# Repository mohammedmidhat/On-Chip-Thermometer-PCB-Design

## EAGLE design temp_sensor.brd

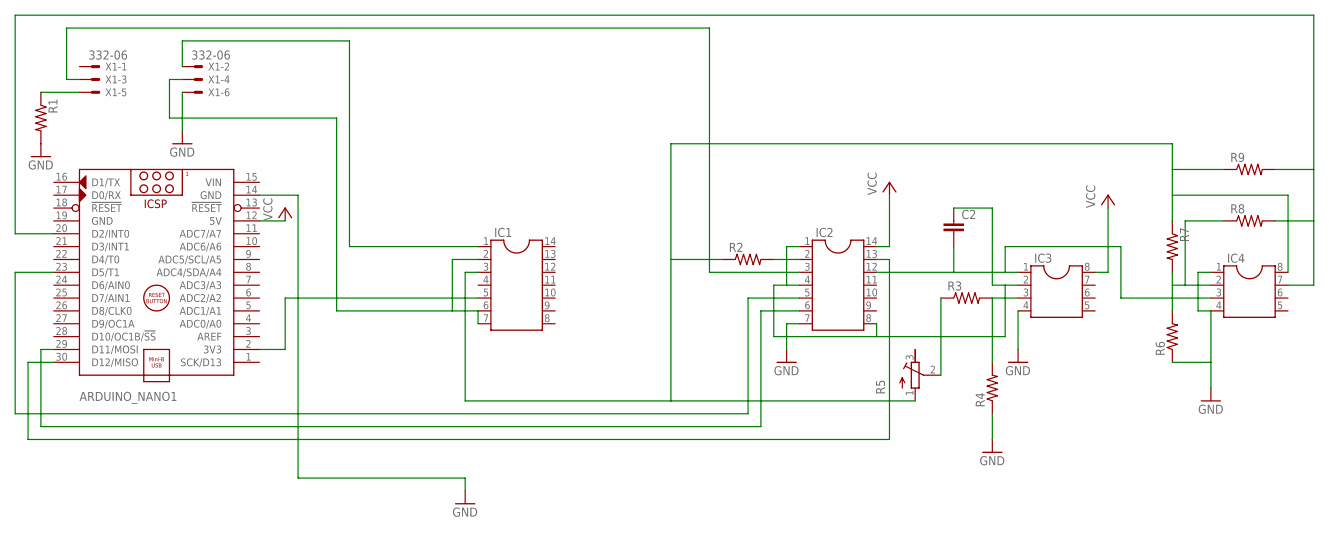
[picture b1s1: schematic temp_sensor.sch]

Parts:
ARDUINO_NANO1: ARDUINO_NANO
C2: C5/2.5; C5B2.5
IC1, IC2: DIL14
IC3, IC4: DIL8; DIL08
R1, R2, R3, R4, R6, R7, R8, R9: R-US_0207/10; 0207/10
R5: R-TRIMM3299W; RTRIM3299W
X1: 332-06

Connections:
GND: ARDUINO_NANO1.14 (GND), ARDUINO_NANO1.19 (GND), IC2.7, IC3.4, IC4.1, IC4.4, R1.2, R4.1, R6.1, X1.6
unnamed: IC1.1, X1.2
unnamed: ARDUINO_NANO1.2 (3V3), IC1.3, IC1.5, IC4.8, R2.1, R5.1 (A), R7.1, R9.1
unnamed: IC1.2, IC1.6, IC1.7, X1.4
unnamed: ARDUINO_NANO1.23 (D5/T1), IC2.5
unnamed: R1.1, X1.5
unnamed: IC2.3, X1.3
unnamed: ARDUINO_NANO1.30 (D12/MISO), IC2.13
unnamed: ARDUINO_NANO1.29 (D11/MOSI), IC2.6
unnamed: C2.1, IC2.1, IC2.4, IC2.8, IC3.2
unnamed: C2.2, IC2.12, IC3.1, IC4.3
unnamed: IC2.2, R2.2
unnamed: IC3.3, R3.2, R4.2
unnamed: R3.1, R5.2 (S)
unnamed: IC4.2, R6.2, R7.2, R8.1
unnamed: ARDUINO_NANO1.20 (D2/INT0), IC4.7, R8.2, R9.2
VCC: ARDUINO_NANO1.12 (5V), IC2.14, IC3.8
VIN: ARDUINO_NANO1.15 (VIN)

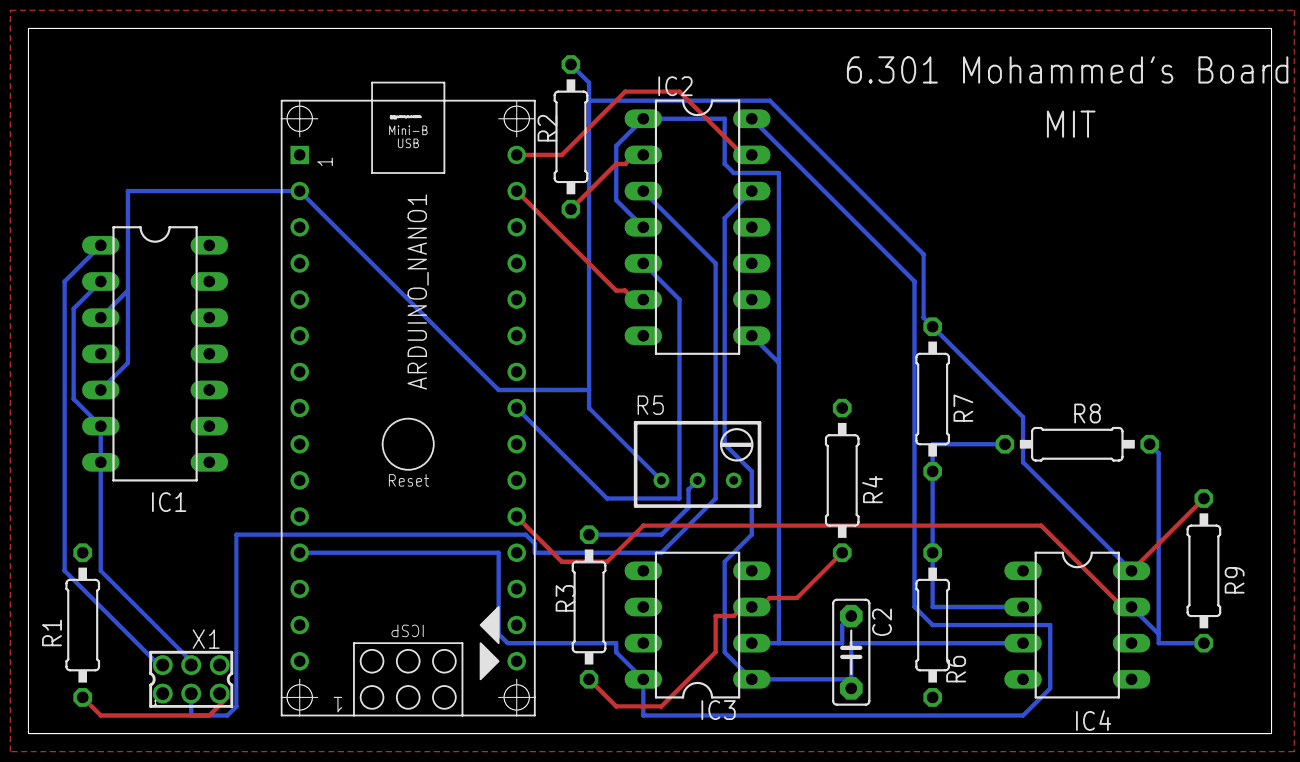
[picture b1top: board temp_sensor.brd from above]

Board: 2 copper layers, 87.3 x 49.5 mm, 16 parts (0 on the bottom side), 17 nets.

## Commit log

2016-12-15 all the files uploaded
